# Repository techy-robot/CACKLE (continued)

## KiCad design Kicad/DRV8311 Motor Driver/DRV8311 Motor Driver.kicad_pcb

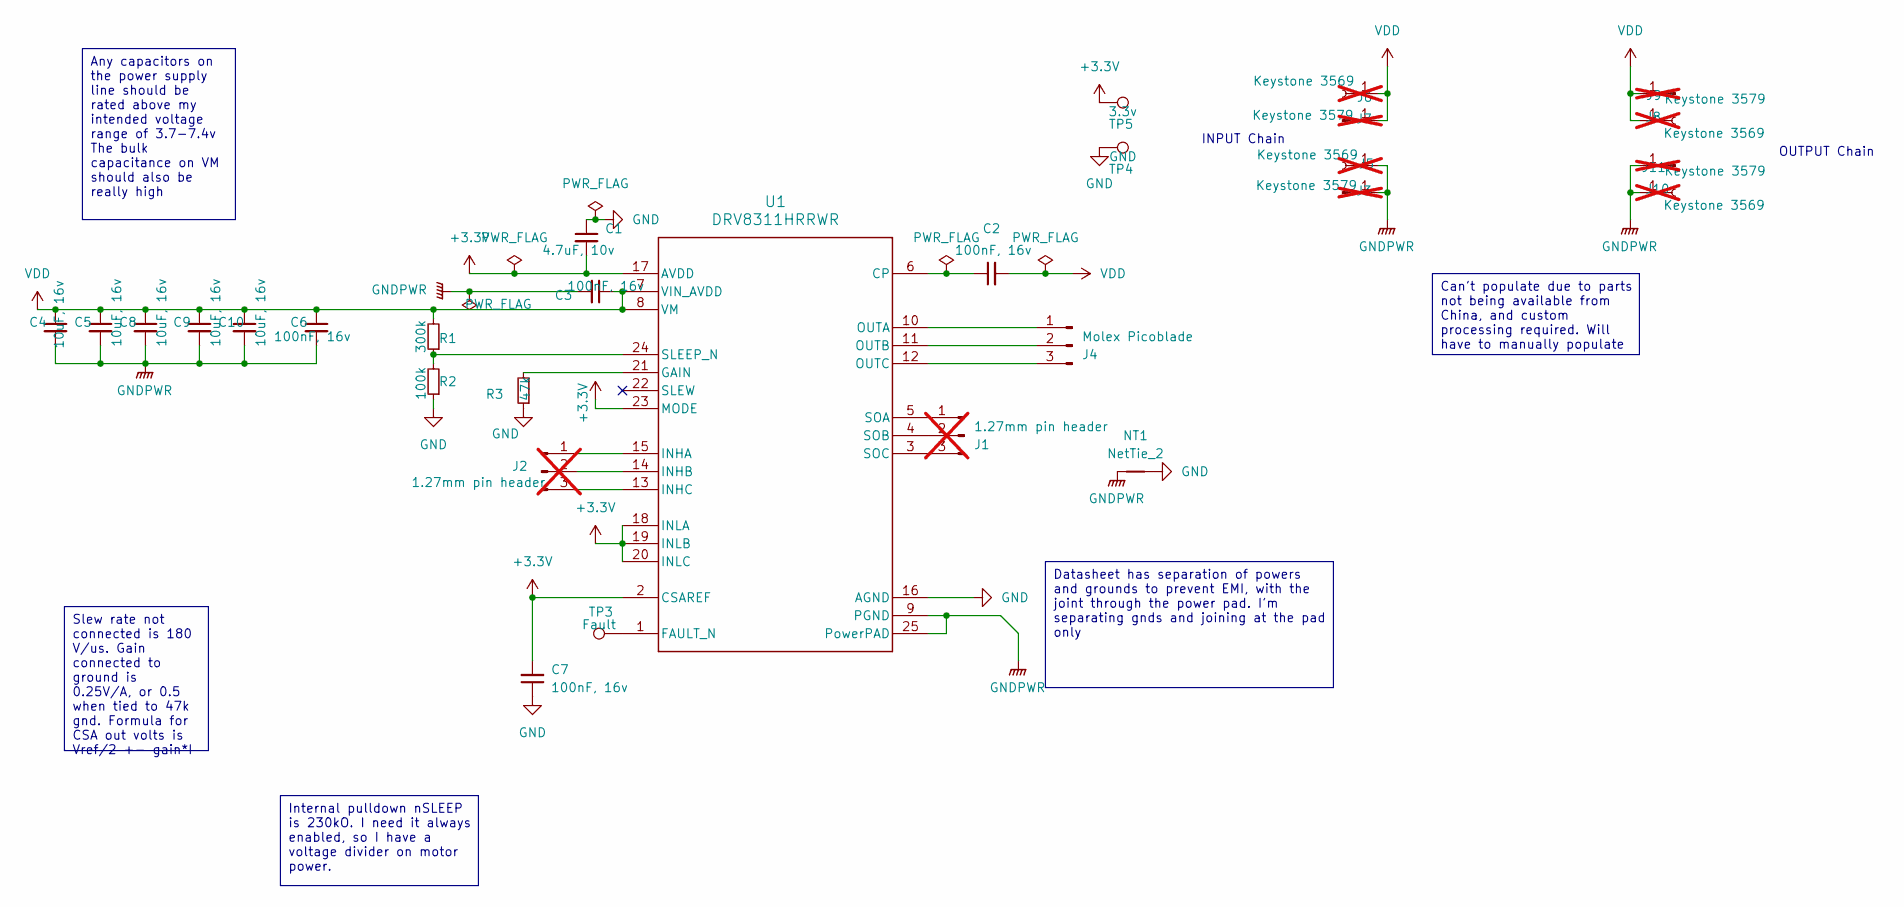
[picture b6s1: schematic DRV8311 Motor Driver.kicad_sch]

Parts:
C1: 4.7uF, 10v; C_0402_1005Metric
C2, C6: 100nF, 16v; C_0603_1608Metric
C3, C7: 100nF, 16v; C_0402_1005Metric
C4, C5, C8, C9, C10: 10uF, 16v; C_0603_1608Metric
J1, J2: 1.27mm pin header; PinHeader_1x03_P1.27mm_Horizontal; not fitted
J3, J7, J9, J11: Keystone 3579; Keystone_3579; not fitted
J4: Molex Picoblade; Molex_PicoBlade_53048-0310_1x03_P1.25mm_Horizontal
J5, J6, J8, J10: Keystone 3569; Keystone_3569_half; not fitted
NT1: NetTie_2; NetTie-2_SMD_Pad0.2mm
R1: 300k; R_0402_1005Metric
R2: 100k; R_0402_1005Metric
R3: 47k; R_0402_1005Metric
TP3: Fault; TestPoint_Pad_D1.0mm
TP4: GND; TestPoint_Pad_D1.0mm
TP5: 3.3v; TestPoint_Pad_D1.0mm
U1: DRV8311HRRWR; DRV8311_0.3mmVias

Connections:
+3.3V: C1.2, C7.2, TP5.1, U1.2 (CSAREF), U1.17 (AVDD), U1.18 (INLA), U1.19 (INLB), U1.20 (INLC), U1.23 (MODE)
GND: C1.1, C7.1, NT1.2, R2.1, R3.1, TP4.1, U1.16 (AGND)
GNDPWR: C3.2, C4.2, C5.2, C6.2, C8.2, C9.2, C10.2, J3.1, J5.1, J10.1, J11.1, NT1.1, U1.9 (PGND), U1.25 (PowerPAD)
unnamed: J1.1, U1.5 (SOA)
unnamed: J1.2, U1.4 (SOB)
unnamed: J1.3, U1.3 (SOC)
unnamed: J2.1, U1.15 (INHA)
unnamed: J2.2, U1.14 (INHB)
unnamed: J2.3, U1.13 (INHC)
unnamed: J4.1, U1.10 (OUTA)
unnamed: J4.2, U1.11 (OUTB)
unnamed: J4.3, U1.12 (OUTC)
unnamed: C2.1, U1.6 (CP)
unnamed: TP3.1, U1.1 (FAULT_N)
unnamed: R3.2, U1.21 (GAIN)
unnamed: R1.1, R2.2, U1.24 (SLEEP_N)
VDD: C2.2, C3.1, C4.1, C5.1, C6.1, C8.1, C9.1, C10.1, J6.1, J7.1, J8.1, J9.1, R1.2, U1.7 (VIN_AVDD), U1.8 (VM)

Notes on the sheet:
Internal pulldown nSLEEP is 230kO. I need it always enabled, so I have a voltage divider on motor power.
Can't populate due to parts not being available from China, and custom processing required. Will have to manually populate
Slew rate not connected is 180 V/us. Gain connected to ground is 0.25V/A, or 0.5 when tied to 47k gnd. Formula for CSA out volts is Vref/2 +- gain*I
Datasheet has separation of powers and grounds to prevent EMI, with the joint through the power pad. I'm separating gnds and joining at the pad only
Any capacitors on the power supply line should be rated above my intended voltage range of 3.7-7.4v The bulk capacitance on VM should also be really high
INPUT Chain
OUTPUT Chain

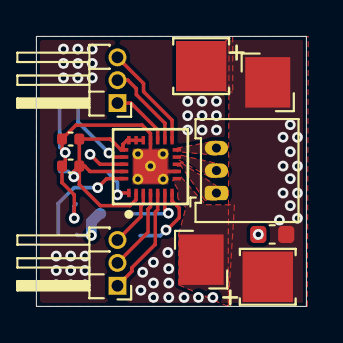
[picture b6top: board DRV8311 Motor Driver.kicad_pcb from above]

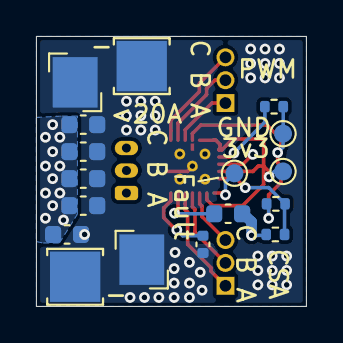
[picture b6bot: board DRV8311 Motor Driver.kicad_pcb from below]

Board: 4 copper layers, 15.0 x 15.0 mm, 29 parts (17 on the bottom side), 17 nets.

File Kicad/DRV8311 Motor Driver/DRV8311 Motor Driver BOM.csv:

"Id";"Designator";"Footprint";"Quantity";"Designation";"Supplier and ref";
1;"J7,J9,J3,J11";"Keystone_3579";4;"Keystone 3579";;;
2;"J4";"Molex_PicoBlade_53048-0310_1x03_P1.25mm_Horizontal";1;"Molex Picoblade";;;
3;"C1";"C_0402_1005Metric";1;"4.7uF, 10v";;;
4;"U1";"DRV8311_0.3mmVias";1;"DRV8311HRRWR";;;
5;"J8,J6,J10,J5";"Keystone_3569_half";4;"Keystone 3569";;;
6;"C6,C2";"C_0603_1608Metric";2;"100nF, 16v";;;
7;"J2,J1";"PinHeader_1x03_P1.27mm_Horizontal";2;"1.27mm pin header";;;
8;"C7,C3";"C_0402_1005Metric";2;"100nF, 16v";;;
9;"R1";"R_0402_1005Metric";1;"300k";;;
10;"C4,C9,C10,C8,C5";"C_0603_1608Metric";5;"10uF, 16v";;;
11;"R3";"R_0402_1005Metric";1;"47k";;;
12;"R2";"R_0402_1005Metric";1;"100k";;;

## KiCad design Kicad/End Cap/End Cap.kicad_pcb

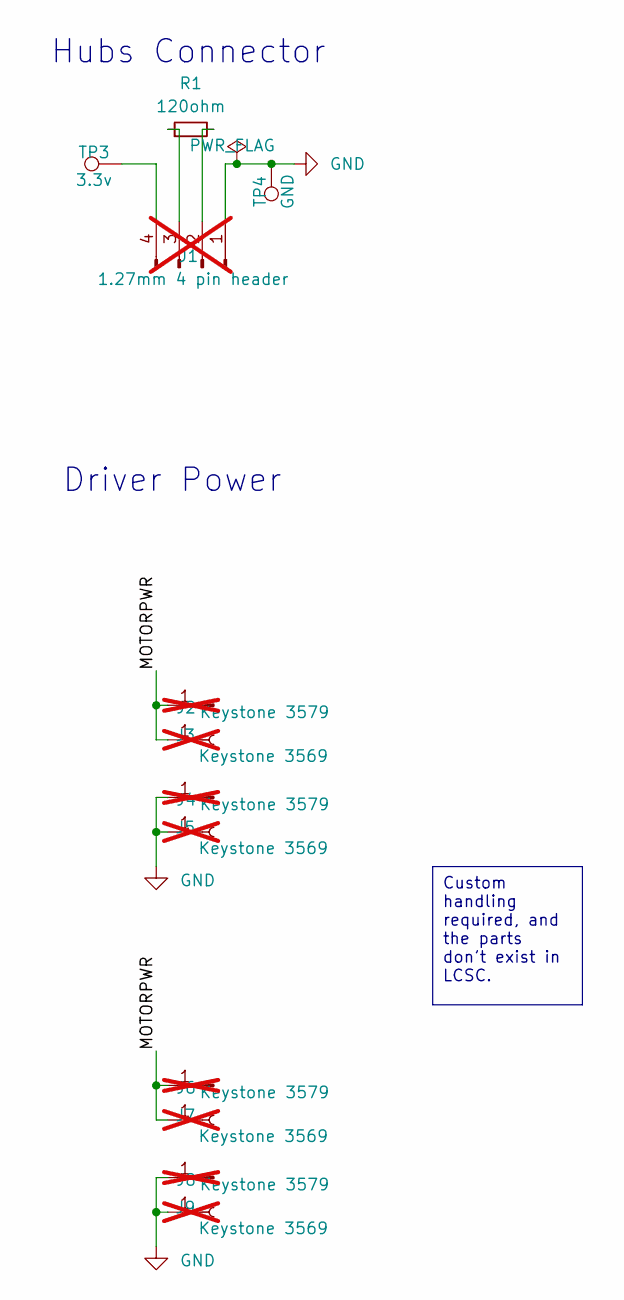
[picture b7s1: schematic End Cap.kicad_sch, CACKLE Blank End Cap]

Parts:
J1: 1.27mm 4 pin header; PinHeader_1x04_P1.27mm_Vertical; not fitted
J2, J4, J6, J8: Keystone 3579; Keystone_3579; not fitted
J3, J5, J7, J9: Keystone 3569; Keystone_3569_half; not fitted
R1: 120ohm; R_0402_1005Metric; LCSC C25079
TP3: 3.3v; TestPoint_Pad_D1.0mm
TP4: GND; TestPoint_Pad_D1.0mm

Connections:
/MOTORPWR: J2.1, J3.1, J6.1, J7.1
GND: J1.1, J4.1, J5.1, J8.1, J9.1, TP4.1
unnamed: J1.2, R1.2
unnamed: J1.3, R1.1
unnamed: J1.4, TP3.1

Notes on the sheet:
Custom handling required, and the parts don't exist in LCSC.
Hubs Connector
Driver Power

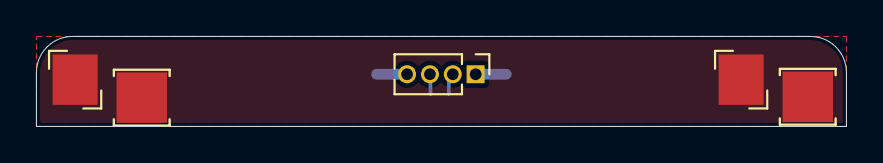
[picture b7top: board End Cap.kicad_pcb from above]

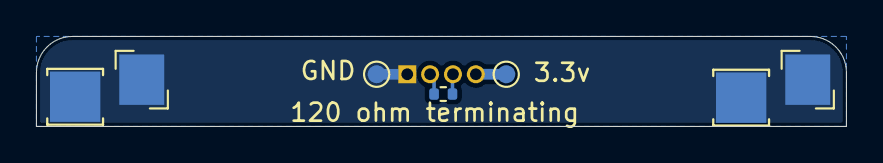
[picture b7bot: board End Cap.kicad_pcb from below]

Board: 2 copper layers, 45.0 x 5.0 mm, 12 parts (7 on the bottom side), 5 nets.

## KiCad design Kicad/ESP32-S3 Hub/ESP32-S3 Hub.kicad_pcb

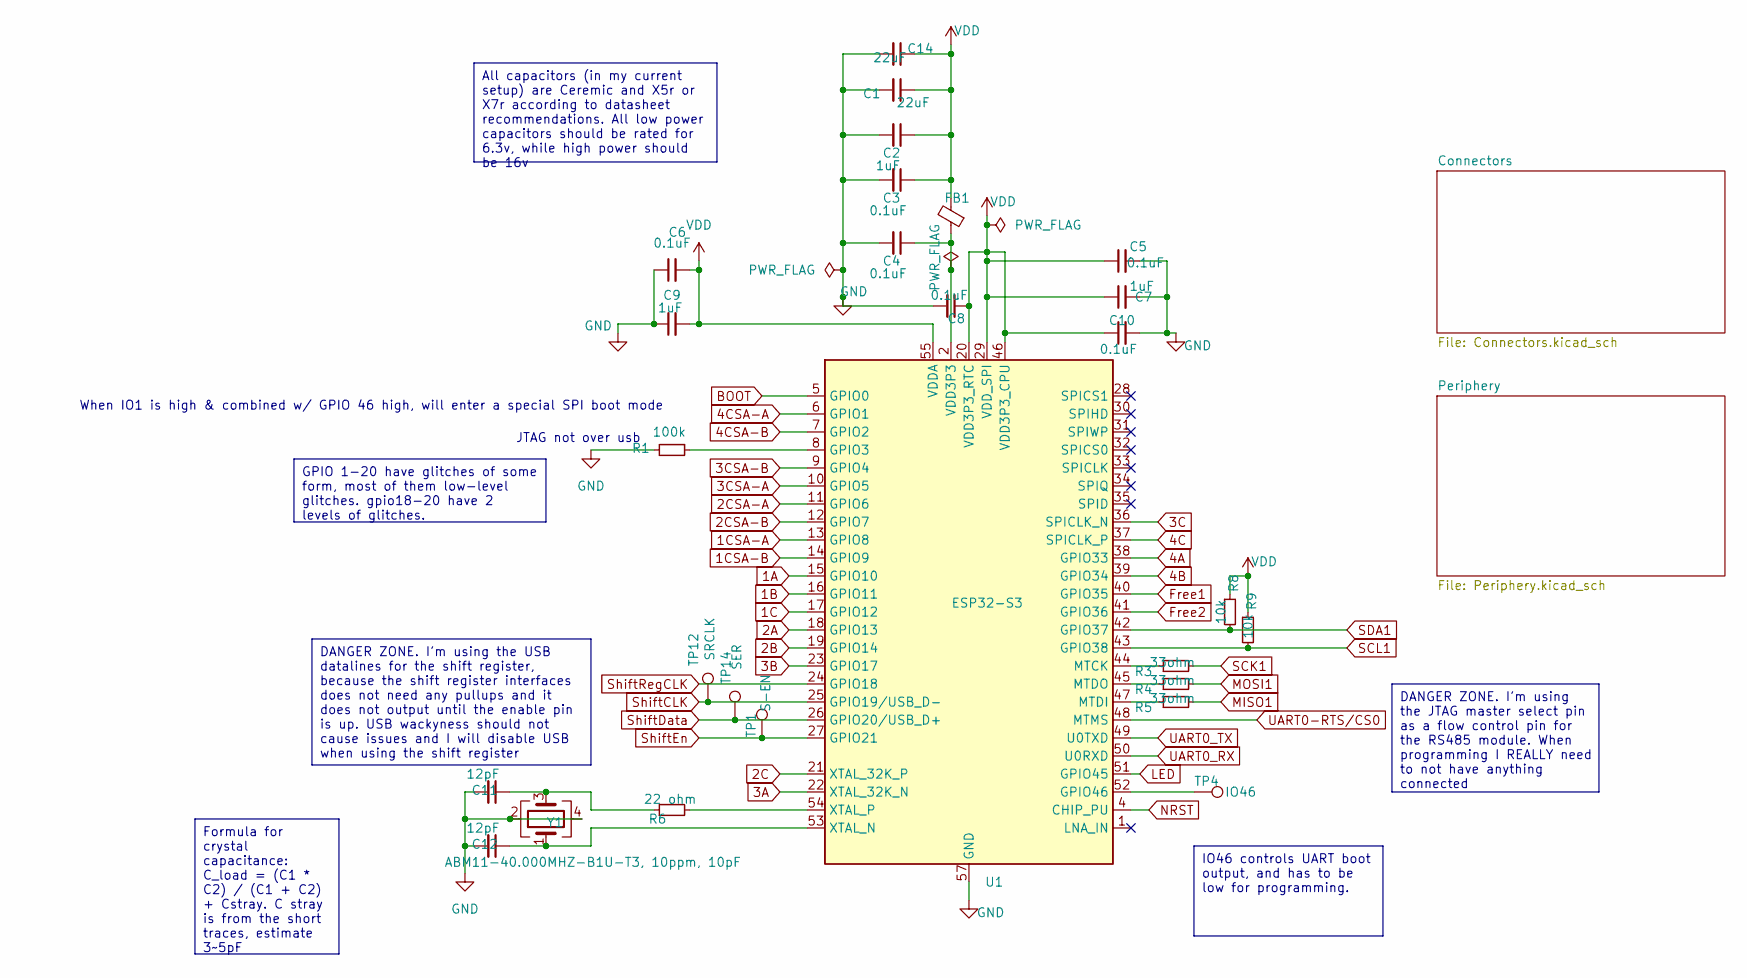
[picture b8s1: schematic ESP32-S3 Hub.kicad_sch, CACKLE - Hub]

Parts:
C1, C14: 22uF; C_0402_1005Metric
C2, C7, C9: 1uF; C_0402_1005Metric
C3, C4, C5, C6, C8, C10: 0.1uF; C_0402_1005Metric
C11, C12: 12pF; C_0402_1005Metric
FB1: 120ohm imp @100mhz, 1 amp; L_0402_1005Metric
R1: 100k; R_0402_1005Metric
R3, R4, R5: 33ohm; R_0402_1005Metric
R6: 22 ohm; R_0402_1005Metric
R8, R9: 10k; R_0402_1005Metric
TP1: S-EN; TestPoint_Pad_D1.0mm
TP4: IO46; TestPoint_Pad_D1.0mm
TP12: SRCLK; TestPoint_Pad_D1.0mm
TP14: SER; TestPoint_Pad_D1.0mm
U1: ESP32-S3; QFN-56-1EP_7x7mm_P0.4mm_EP4x4mm
Y1: ABM11-40.000MHZ-B1U-T3, 10ppm, 10pF; Crystal_SMD_2016-4Pin_2.0x1.6mm

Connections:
1A: U1.15 (GPIO10); also elsewhere on the board
1B: U1.16 (GPIO11); also elsewhere on the board
1C: U1.17 (GPIO12); also elsewhere on the board
1CSA-A: U1.13 (GPIO8); also elsewhere on the board
1CSA-B: U1.14 (GPIO9); also elsewhere on the board
2A: U1.18 (GPIO13); also elsewhere on the board
2B: U1.19 (GPIO14); also elsewhere on the board
2C: U1.21 (XTAL_32K_P); also elsewhere on the board
2CSA-A: U1.11 (GPIO6); also elsewhere on the board
2CSA-B: U1.12 (GPIO7); also elsewhere on the board
3A: U1.22 (XTAL_32K_N); also elsewhere on the board
3B: U1.23 (GPIO17); also elsewhere on the board
3C: U1.36 (SPICLK_N); also elsewhere on the board
3CSA-A: U1.10 (GPIO5); also elsewhere on the board
3CSA-B: U1.9 (GPIO4); also elsewhere on the board
4A: U1.38 (GPIO33); also elsewhere on the board
4B: U1.39 (GPIO34); also elsewhere on the board
4C: U1.37 (SPICLK_P); also elsewhere on the board
4CSA-A: U1.6 (GPIO1); also elsewhere on the board
4CSA-B: U1.7 (GPIO2); also elsewhere on the board
BOOT: U1.5 (GPIO0); also elsewhere on the board
Free1: U1.40 (GPIO35); also elsewhere on the board
Free2: U1.41 (GPIO36); also elsewhere on the board
GND: C1.2, C2.2, C3.2, C4.2, C5.2, C6.1, C7.2, C8.2, C9.1, C10.2, C11.2, C12.2, C14.2, R1.2, U1.57 (GND), Y1.2, Y1.4; also elsewhere on the board
LED: U1.51 (GPIO45); also elsewhere on the board
MISO1: R5.2; also elsewhere on the board
MOSI1: R4.2; also elsewhere on the board
NRST: U1.4 (CHIP_PU); also elsewhere on the board
unnamed: C4.1, FB1.1, U1.2 (VDD3P3), U1.3 (VDD3P3)
unnamed: C11.1, R6.1, Y1.3
unnamed: R1.1, U1.8 (GPIO3)
unnamed: TP4.1, U1.52 (GPIO46)
unnamed: R3.1, U1.44 (MTCK)
unnamed: R5.1, U1.47 (MTDI)
unnamed: R4.1, U1.45 (MTDO)
unnamed: C12.1, U1.53 (XTAL_N), Y1.1
unnamed: R6.2, U1.54 (XTAL_P)
SCK1: R3.2; also elsewhere on the board
SCL1: R9.2, U1.43 (GPIO38); also elsewhere on the board
SDA1: R8.2, U1.42 (GPIO37); also elsewhere on the board
ShiftCLK: TP12.1, U1.25 (GPIO19/USB_D-); also elsewhere on the board
ShiftData: TP14.1, U1.26 (GPIO20/USB_D+); also elsewhere on the board
ShiftEn: TP1.1, U1.27 (GPIO21); also elsewhere on the board
ShiftRegCLK: U1.24 (GPIO18); also elsewhere on the board
UART0-RTS/CS0: U1.48 (MTMS); also elsewhere on the board
UART0_RX: U1.50 (U0RXD); also elsewhere on the board
UART0_TX: U1.49 (U0TXD); also elsewhere on the board
VDD: C1.1, C2.1, C3.1, C5.1, C6.2, C7.1, C8.1, C9.2, C10.1, C14.1, FB1.2, R8.1, R9.1, U1.20 (VDD3P3_RTC), U1.29 (VDD_SPI), U1.46 (VDD3P3_CPU), U1.55 (VDDA), U1.56 (VDDA); also elsewhere on the board

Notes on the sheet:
DANGER ZONE. I'm using the JTAG master select pin as a flow control pin for the RS485 module. When programming I REALLY need to not have anything connected
DANGER ZONE. I'm using the USB datalines for the shift register, because the shift register interfaces does not need any pullups and it does not output until the enable pin is up. USB wackyness should not cause issues and I will disable USB when using the shift register
All capacitors (in my current setup) are Ceremic and X5r or X7r according to datasheet recommendations. All low power capacitors should be rated for 6.3v, while high power should be 16v
IO46 controls UART boot output, and has to be low for programming.
GPIO 1-20 have glitches of some form, most of them low-level glitches. gpio18-20 have 2 levels of glitches.
Formula for crystal capacitance: C_load = (C1 * C2) / (C1 + C2) + Cstray. C stray is from the short traces, estimate 3~5pF
JTAG not over usb
When IO1 is high & combined w/ GPIO 46 high, will enter a special SPI boot mode

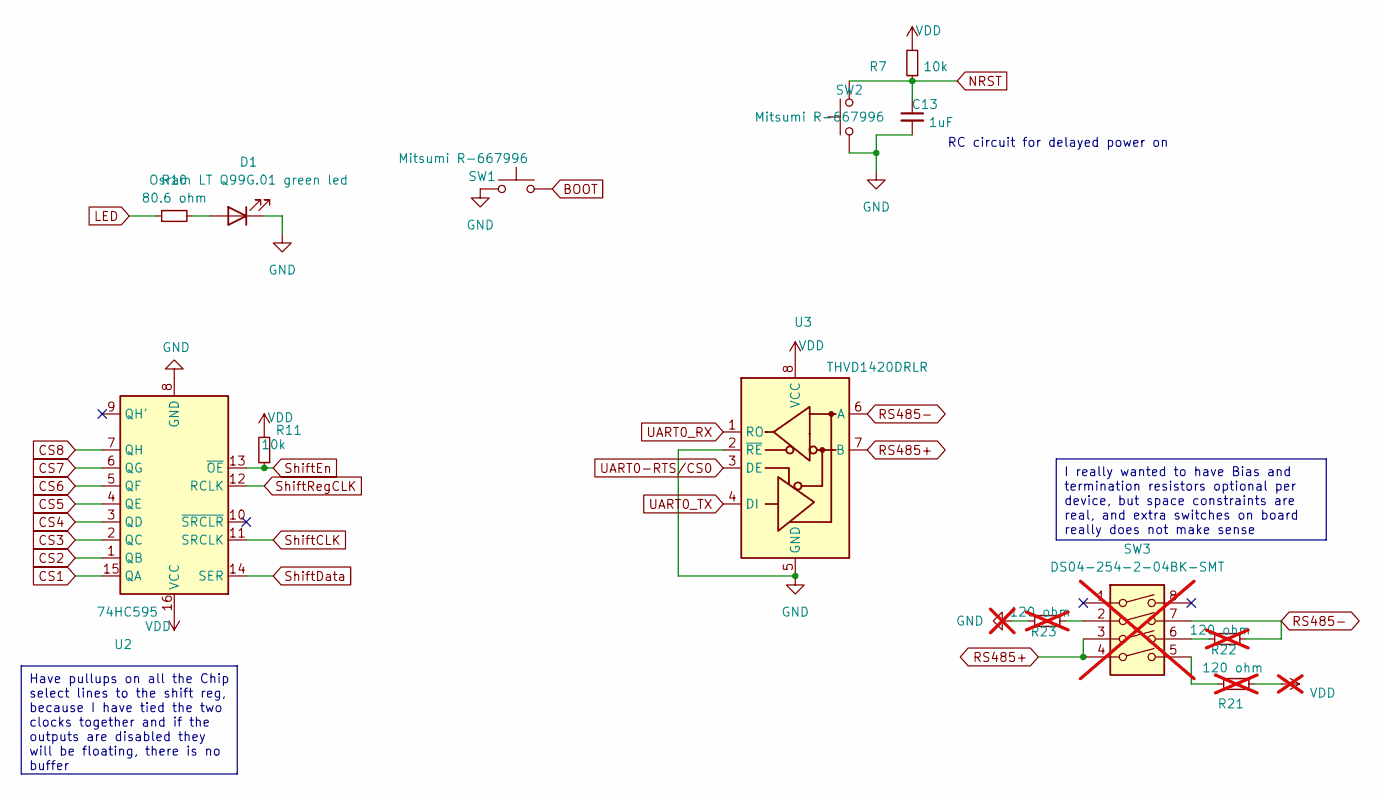
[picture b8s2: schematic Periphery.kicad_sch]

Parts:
C13: 1uF; C_0402_1005Metric
D1: Osram LT Q99G.01 green led; LED_0603_1608Metric_Pad1.05x0.95mm_HandSolder
R7, R11: 10k; R_0402_1005Metric
R10: 80.6 ohm; R_0402_1005Metric
R21, R22, R23: 120 ohm; R_0402_1005Metric; not fitted
SW1, SW2: Mitsumi R-667996; R-667995_MIT
SW3: DS04-254-2-04BK-SMT; SW_DIP_SPSTx04_Slide_Omron_A6S-410x_W8.9mm_P2.54mm; not fitted
U2: 74HC595; DHVQFN-16-1EP_2.5x3.5mm_P0.5mm_EP1x2mm
U3: THVD1420DRLR; SOT-583-8

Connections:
BOOT: SW1.2; also elsewhere on the board
CS1: U2.15 (QA); also elsewhere on the board
CS2: U2.1 (QB); also elsewhere on the board
CS3: U2.2 (QC); also elsewhere on the board
CS4: U2.3 (QD); also elsewhere on the board
CS5: U2.4 (QE); also elsewhere on the board
CS6: U2.5 (QF); also elsewhere on the board
CS7: U2.6 (QG); also elsewhere on the board
CS8: U2.7 (QH); also elsewhere on the board
GND: C13.2, D1.1 (K), R23.2, SW1.1, SW2.1, U2.8 (GND), U2.17 (GND), U3.2 (~RE), U3.5 (GND); also elsewhere on the board
LED: R10.1; also elsewhere on the board
NRST: C13.1, R7.1, SW2.2; also elsewhere on the board
unnamed: D1.2 (A), R10.2
unnamed: R21.2, SW3.5
unnamed: R22.2, SW3.6
unnamed: R23.1, SW3.2
RS485+: SW3.3, SW3.4, U3.7 (B); also elsewhere on the board
RS485-: R22.1, SW3.7, U3.6 (A); also elsewhere on the board
ShiftCLK: U2.11 (SRCLK); also elsewhere on the board
ShiftData: U2.14 (SER); also elsewhere on the board
ShiftEn: R11.1, U2.13 (~OE); also elsewhere on the board
ShiftRegCLK: U2.12 (RCLK); also elsewhere on the board
UART0-RTS/CS0: U3.3 (DE); also elsewhere on the board
UART0_RX: U3.1 (RO); also elsewhere on the board
UART0_TX: U3.4 (DI); also elsewhere on the board
VDD: R7.2, R11.2, R21.1, U2.16 (VCC), U3.8 (VCC); also elsewhere on the board

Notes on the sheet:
Have pullups on all the Chip select lines to the shift reg, because I have tied the two clocks together and if the outputs are disabled they will be floating, there is no buffer
I really wanted to have Bias and termination resistors optional per device, but space constraints are real, and extra switches on board really does not make sense
RC circuit for delayed power on

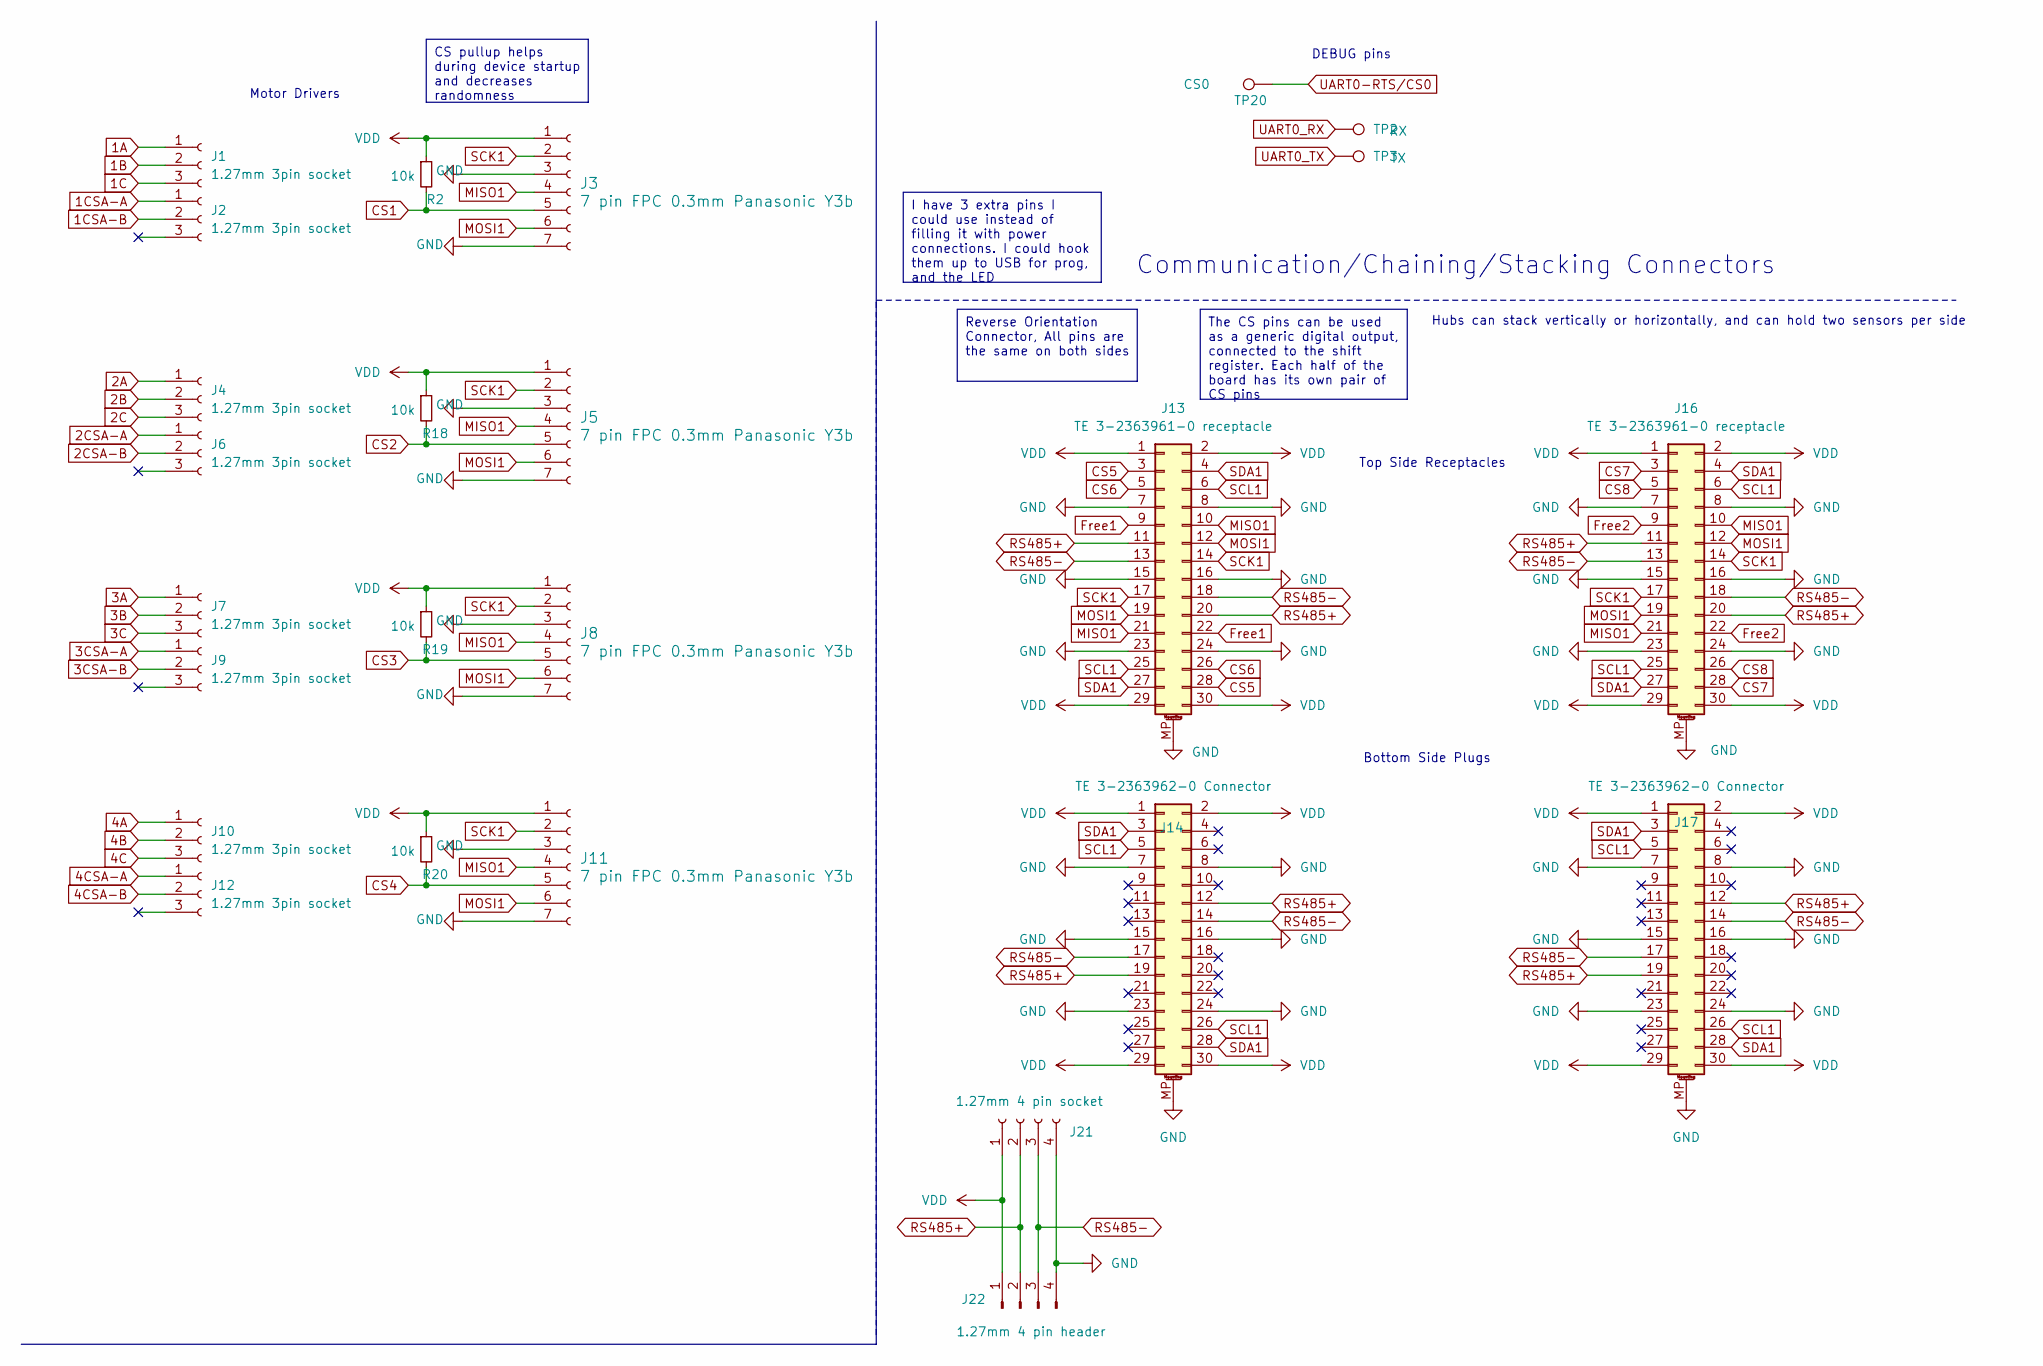
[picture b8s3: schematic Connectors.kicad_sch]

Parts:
J1, J2, J4, J6, J7, J9, J10, J12: 1.27mm 3pin socket; PinHeader_1x03_P1.27mm_Vertical
J3, J5, J8, J11: 7 pin FPC 0.3mm Panasonic Y3b; fpc_7pin_0.3mm_connector Panasonic
J13, J16: TE 3-2363961-0 receptacle; TE_mezzanine_rec_3-2363961-0
J14, J17: TE 3-2363962-0 Connector; TE_mezzanine_conn_3-2363962-0
J21: 1.27mm 4 pin socket; PinSocket_1x04_P1.27mm_Vertical
J22: 1.27mm 4 pin header; PinHeader_1x04_P1.27mm_Horizontal
R2, R18, R19, R20: 10k; R_0402_1005Metric
TP2: RX; TestPoint_Pad_D1.0mm
TP3: TX; TestPoint_Pad_D1.0mm
TP20: CS0; TestPoint_Pad_D1.0mm

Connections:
1A: J1.1; also elsewhere on the board
1B: J1.2; also elsewhere on the board
1C: J1.3; also elsewhere on the board
1CSA-A: J2.1; also elsewhere on the board
1CSA-B: J2.2; also elsewhere on the board
2A: J4.1; also elsewhere on the board
2B: J4.2; also elsewhere on the board
2C: J4.3; also elsewhere on the board
2CSA-A: J6.1; also elsewhere on the board
2CSA-B: J6.2; also elsewhere on the board
3A: J7.1; also elsewhere on the board
3B: J7.2; also elsewhere on the board
3C: J7.3; also elsewhere on the board
3CSA-A: J9.1; also elsewhere on the board
3CSA-B: J9.2; also elsewhere on the board
4A: J10.1; also elsewhere on the board
4B: J10.2; also elsewhere on the board
4C: J10.3; also elsewhere on the board
4CSA-A: J12.1; also elsewhere on the board
4CSA-B: J12.2; also elsewhere on the board
CS1: J3.5, R2.2; also elsewhere on the board
CS2: J5.5, R18.2; also elsewhere on the board
CS3: J8.5, R19.2; also elsewhere on the board
CS4: J11.5, R20.2; also elsewhere on the board
CS5: J13.3, J13.28; also elsewhere on the board
CS6: J13.5, J13.26; also elsewhere on the board
CS7: J16.3, J16.28; also elsewhere on the board
CS8: J16.5, J16.26; also elsewhere on the board
Free1: J13.9, J13.22; also elsewhere on the board
Free2: J16.9, J16.22; also elsewhere on the board
GND: J3.3, J3.7, J5.3, J5.7, J8.3, J8.7, J11.3, J11.7, J13.7, J13.8, J13.15, J13.16, J13.23, J13.24, J13.MP (MountPin), J14.7, J14.8, J14.15, J14.16, J14.23, J14.24, J14.MP (MountPin), J16.7, J16.8, J16.15, J16.16, J16.23, J16.24, J16.MP (MountPin), J17.7, J17.8, J17.15, J17.16, J17.23, J17.24, J17.MP (MountPin), J21.4, J22.4; also elsewhere on the board
MISO1: J3.4, J5.4, J8.4, J11.4, J13.10, J13.21, J16.10, J16.21; also elsewhere on the board
MOSI1: J3.6, J5.6, J8.6, J11.6, J13.12, J13.19, J16.12, J16.19; also elsewhere on the board
RS485+: J13.11, J13.20, J14.12, J14.19, J16.11, J16.20, J17.12, J17.19, J21.2, J22.2; also elsewhere on the board
RS485-: J13.13, J13.18, J14.14, J14.17, J16.13, J16.18, J17.14, J17.17, J21.3, J22.3; also elsewhere on the board
SCK1: J3.2, J5.2, J8.2, J11.2, J13.14, J13.17, J16.14, J16.17; also elsewhere on the board
SCL1: J13.6, J13.25, J14.5, J14.26, J16.6, J16.25, J17.5, J17.26; also elsewhere on the board
SDA1: J13.4, J13.27, J14.3, J14.28, J16.4, J16.27, J17.3, J17.28; also elsewhere on the board
UART0-RTS/CS0: TP20.1; also elsewhere on the board
UART0_RX: TP2.1; also elsewhere on the board
UART0_TX: TP3.1; also elsewhere on the board
VDD: J3.1, J5.1, J8.1, J11.1, J13.1, J13.2, J13.29, J13.30, J14.1, J14.2, J14.29, J14.30, J16.1, J16.2, J16.29, J16.30, J17.1, J17.2, J17.29, J17.30, J21.1, J22.1, R2.1, R18.1, R19.1, R20.1; also elsewhere on the board

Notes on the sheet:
Reverse Orientation Connector, All pins are the same on both sides
CS pullup helps during device startup and decreases randomness
The CS pins can be used as a generic digital output, connected to the shift register. Each half of the board has its own pair of CS pins
I have 3 extra pins I could use instead of filling it with power connections. I could hook them up to USB for prog, and the LED
Communication/Chaining/Stacking Connectors
Top Side Receptacles
Motor Drivers
Hubs can stack vertically or horizontally, and can hold two sensors per side
DEBUG pins
Bottom Side Plugs

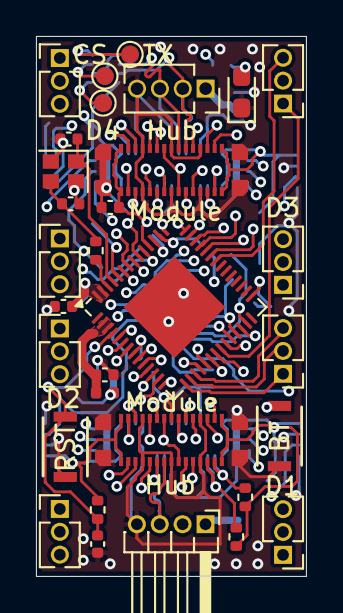
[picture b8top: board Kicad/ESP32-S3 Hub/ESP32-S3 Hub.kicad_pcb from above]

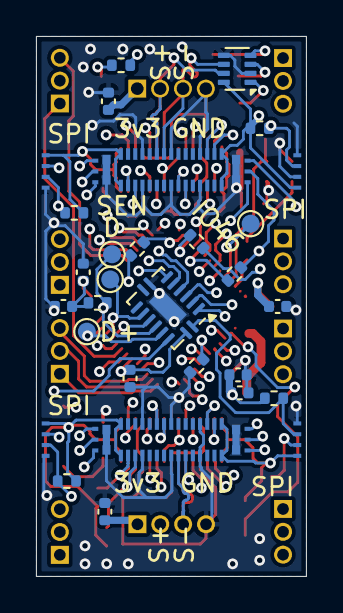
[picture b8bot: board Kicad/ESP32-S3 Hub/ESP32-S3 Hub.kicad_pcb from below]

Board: 6 copper layers, 15.0 x 30.0 mm, 61 parts (30 on the bottom side), 59 nets.

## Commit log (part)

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2024-09-17 Initial Documentation
2024-09-24 Added missing media, update Project goals
    I also added a new sketch of the architecture
2024-09-24 Added note on project management
2024-09-24 Initial adaption of DRV8311 board
    I had this from a previous test pcb. It works really well after fixing the errata, so I will only make a few minor changes to the physical design for the card.
2024-09-24 Replaced external connectors
    I have keystone smd low profile contacts for the power, and 1.27mm pitch headers for the data pins.
2024-09-24 Finished basic layout for motor driver card
    The power connectors as of now have no way of contacting adjacent cards. The layout will need some tuning, but I think the components for the most part can stay in the same place.
2024-09-25 Finished basic routing
    I still need to optimize it, and work out how to improve conductivity and thermal properties
2024-09-26 Finished silkscreen, adjusted component placements and vias
2024-10-13 Fixed ERC errors, stopped tracking a few .obsidian files
    The only errors that popped up were the dual labeling of CS0 and Uart RTS, a power flag spot, and a modified footprint error.
2024-10-14 Switched out Mezzanine Connectors
    I'm going with some 30-pin TE mezzanine connectors, which are cheaper than before and have a few extra pins if I need them in the future.
2024-10-14 Started Layout
    I added the footprints on the PCB file. My goal is to fit everything within a 15x30mm package. We will see!
2024-10-16 Finished basic layout
    Everything is crammed in there, I do have some extras bit of space up top for an extra component or two. I probably should take advantage of that space somehow. For routing this thing, I really think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
2024-10-18 Swapping register pins
    I tryid to simplify the layout a little bit. I also added a note about the potential danger of the i2c lines on low level glitching pins.
2024-10-18 Switched to 6 layer design
    I still need to arrange the stackup correctly
2024-10-19 Changed layer stack
    I now have a layer stack of Sig/Gnd/Sig/Pwr/Gnd/Sig, which appears to be a common arrangement except I've reversed the order. I added a lot of signals in the middle of the power layer though, because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
    I also connected Free2 to the correct connectors in the schematic, something I missed when I changed the esp32 pin assignments.
2024-10-19 Removed unneeded via for CS2
    I routed directly to the connector, no via necessary.
2024-10-19 Routed Current Sense lines
2024-10-19 Shifting vias to route i2c
    I spent a solid 3 hours trying to get this one trace through without cutting off other traces, finally managed to do it now. It was a lot of playing around with vias until everything fit.
2024-10-19 Routed UART, buttons, and flipped analog power cap
    I needed a capacitor near the power input at the top, because otherwise the power is flowing directly from the plane through the one via. I'm still not sure that I've fixed a problem, its seems likel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
2024-10-19 Swapped header logical numbers
    I realized my numbering scheme was off with the actual board layout. So in the schematic I swapped the connectors without rewiring so that the numbers are more logical. CS7, CS8, and Free2 are now fo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
2024-10-20 Finished routing PWM motor pins
    I did have to sacrifice the continuity of one of my ground planes to make it happen though. I tried to keep it to a minimum
2024-10-20 Cleaned up wires, added IO46 testpad, added license to design files
    I also added a ground plane to In3.
2024-10-20 Removed problem connections on bottom connector
    We don't want several masters fighting over gpio pins or the SPI bus, so I have removed all connections on the bottom side except the multi-master capable busses.
2024-10-20 Arranged Silkscreen
2024-10-20 Fixing board edge pin header 3d models
    I tried first switching out the footprint entirely, but that resulted in the 3d models pointing in to the board. I rotated all the connections in the schematic and the board, but that came with a bil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
2024-10-21 Started switchout of motor power connectors
    It looks like I may actually have gotten connectors a bit TOO big! I don't know if it will fit!
2024-10-25 Adjusted copper zones
2024-10-25 Finished Brushed motor driver DRV8213
    It can handle 4 amps, and uses a JST PH connector for the motor.
2024-10-26 Updated docs
2024-10-26 Rearranged schematic hierarchy
    It should be clearer than the original design from my testing board. I haven't changed any of the design things except getting the correct small transistor footprint (errata from before)
2024-11-20 Fixed OE pin by adding pullup, updated silkscreen
    The silkscreen looks really nice now, I have all the port labels.
2024-11-29 Reworked PSU to use CH32X035 and USB-PD
    This will save a few bucks and will actually be a cooler solution than just a DC jack connected to some pads
2024-11-29 Changed onboard mcu regulator
2024-11-30 Add proper ESD protection and pulldowns for USB-C
2024-12-01 Added use of Net Class Directives to speed up routing
    I don't have to manually change wire sizes now
2024-12-01 Updated Sheet Properties
    My author name is now in there, and I've added the proper project name.
2024-12-01 Adjusted board thickness to have 2 oz outer copper and 0.5 oz inner copper
2024-12-18 Update docs
2024-12-18 Added TVS diodes for USB-C
2024-12-20 Switched out always on 3v3 reg to smaller WSON-6
    This is more expensive, but a bit smaller and still has the same input voltage range
2024-12-21 Reorient 3v3 main PSU
2024-12-21 Changed default via sizes
2024-12-21 Disconnect REGN from unneeded output pullups
    These pullups will instead be pulled to 3v3, which should be closer locally. I don't use them but pullups are required for internal detection.
2024-12-21 Fixed Always On PWR connection
    I had it connected to motor power and battery power, what it should have been connected to was USB-C and battery, no barriers whatsoever
2024-12-21 Fixed Logic Pwr netclass
    I had renamed it at some point from "Logic Power" to "Logic Pwr". This messed up some of my net class wire sizes
2024-12-21 Updated 3v3 psu traces and capacitor position
    I rotated the input capacitor to make a more compact shape, and I played around with some of the trace thicknesses
2024-12-22 Combined separate ground planes
    I now have one solid ground plane. There really was no point in having separate ground planes EXCEPT for keeping the high current return path away from the MCU and sense lines. I have added a keepout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
2024-12-23 Finished routing PSU
2024-12-24 Fixed incorrect mosfet pin assignments
    This was an issue from the last test board I designed that I didn't catch. The mosfets have different pin assignments for drain, gate, and source, and I had messed those up in the schematic by choosi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
2024-12-24 Final tweaks, capacitor placement and GND keepouts
    I tried my best to isolate signal grounds from the power paths. I also added a bunch of ground keepouts to help isolate.
2024-12-26 Updating Fab layer text
    I don't know how necessary it is for it to look nice, I started some cleanup
2024-12-26 Added Endcap part w terminating resistor
2024-12-27 Fixed routing of DRV8213 board and updated 3d models
    I swapped the current sense and the PWM input headers accidentally! I fixed that now. I also added the proper 3d models and footprints. I exported a 3d model of the board. The last change I made ws c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
2024-12-28 Updated 3D models and exported 3D model for DRV8311 board
2024-12-28 Updated 3D models and usb length tuning for PSU
    I also tweaked some of the USB length tuning to have the same length at EVERY stop, not just the end. So the through holes should have a matched usb output, and the chip should also have a match.
2024-12-28 Exported 3D model for End Cap
2024-12-28 Created Vertical Sensor board spacer
    I really need to find taller mezzanine connectors that are at least 1.6mm tall, vs the 0.8 currently. It need to just barely stand above the right angle headers.
2024-12-28 Created 2 connector sensor breakout board to avoid needing a spacer
    The bottom is completely flat, and there is little extra room beyond the connectors
2024-12-28 Exported Hub 3d models
2024-12-28 Tweaked some tracks
2024-12-29 Fixed 0.2mm offset in 3d model of Keystone 3579 connector
    It was inset into the pcb a little which was causing some vertical misalignment in the CAD model. This affects nothing in real life, just a nice quality of life thing.
2024-12-31 Added LCSC part numbers, DNP attr, and exported Gerbers
2024-12-31 Fixed Current sense resistor footprints, adjusted current GND blocks
    I had to source alternative resistors and change the footprints as well. I didn't realize though that the 2818 footprint I had was wrong though, 2816 is not quite compatible!
    Another thing I did was fix gnd guides and added horse shoe shapes around the sensitive component vias.
2024-12-31 Rearranged design files
    Instead of "Kicad" the main design folder is now named "Hardware" since I have gerbers and notes besides the kicad files. I have also put my designs in their proper categories.
2024-12-31 Added MA735 encoder nanoSPI device
    This is a new line for what the 7 pin FPC SPI cables are.
2025-01-01 Updated files for JLC DFM checks
2025-01-02 Added schematic PDFs for all boards
2025-01-04 Added gerber zip files
2025-01-13 Added README files for each module
2025-01-13 Changed link names for schematic embeds not displayin
    In Obsidian I can see the pdf embeds perfectly fine, but Github doesn't want to show embedded PDFs. I changed the link alias to "Schematic PDF" so people know what the link is when it doesn't display
2025-02-02 Start on software-hardware definitions
2025-02-03 Added Platformio
2025-02-11 Updated LICENSE terms with CC for images
2025-03-19 Updated architecture
2025-03-19 Added pictures to each module
    Next I need to add readmes for each!
2025-03-19 Created assembly jig
2025-05-06 Added picture with arrows
2025-05-06 Updated MA735 encoder
2025-06-07 Created a dedicated Ideas doc
2025-09-10 Started work on smaller USB only PSU
2025-09-26 Updated plugins
2025-09-26 Started replacement of MCU with STM32
2025-09-30 Finished schematic, started arrangement
2025-09-30 Added USB bus and finished preliminary routing
2025-09-30 revised ground circuit
2025-10-07 Updated connector part ID, added production files
    I messed on on a single number 83 vs 87. The difference is in the plating, and 83 is not available anywhere
2025-10-10 Revert Separation of hardare versions
    This folder versioning will be limited to production files only now
2025-10-10 Started Proto 2 again
2025-10-10 Moved all current production files to Proto 1.
    I haven't made a 2nd prototype yet
2025-10-12 Updated connectors in schem and pcb
2025-10-12 Updated component arrangements and fixed pinout on upstream port
2025-10-17 Add 5mil traces & 0.4mm vias, started via placement
    I am decreasing the size further to speed up routing and avoid pain. The cost will be higher, but not that much higher from 0.3mm to 0.2mm and 0.6mm to 0.4mm vias. I can route more items.
2025-10-17 Fix some track sizes and clearance issues
2025-10-26 Added 2 new stencil jigs
2025-10-26 Swapped out footprints on pcb, started routing
2025-10-31 Added future design expansion comments, re arrange components to fit better
2025-11-01 Swapped around pins and routed main driver outputs
2025-11-01 Finished routing with current components
    I may add some protection and isolation stuff
2025-11-08 Split all boards to sub-modules
2025-11-08 Moved assembly jigs to individual boars
2025-11-08 Updated submodule Hubs/ESP32-S3
2025-11-08 Changed readme to note sub modules and not folders
2025-11-08 Updated submodules
2025-11-08 Changed Docs structure and removed project management
